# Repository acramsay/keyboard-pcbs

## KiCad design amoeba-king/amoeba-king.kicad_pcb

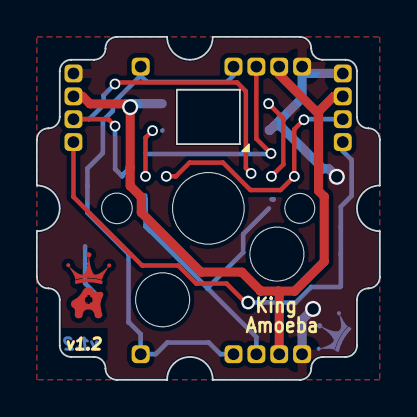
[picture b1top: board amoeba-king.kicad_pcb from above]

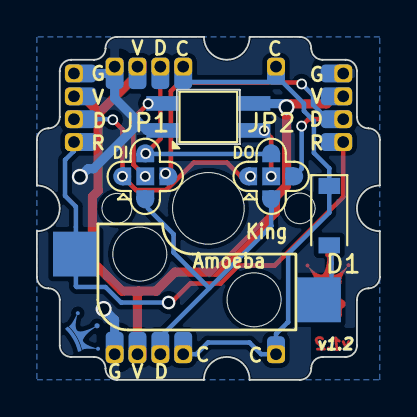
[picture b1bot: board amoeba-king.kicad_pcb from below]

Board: 2 copper layers, 19.0 x 19.1 mm, 14 parts (12 on the bottom side), 11 nets.

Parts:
Amoeba-Logo-Small: G***; amoeba-logo-small
D1: 1N4148W-7-F; D_SOD-123
J1, J4: Conn_01x04_Male; Header_1x04_P1.27mmL
J2, J3: Conn_01x04_Male; Header_1x04_P1.27mm
J5, J6: Conn_01x01_Male; Header_1x01_P1.27mm
JP1, JP2: SolderJumper_5; SolderJumper-5_P1.3mm_Open_RoundedPad1.0x1.5mm
LED1: SK6812MINI_E; LED_SK6812MINI_E_PLCC4_3.2x2.8mm_Shine_Through
Royale: G***; royale
Royale#2: G***; royale
S1: MX1A; Kailh_MX_Socket

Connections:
/C: D1.1 (K), J2.1, J4.1, J5.1, J6.1
/DIN: JP1.2 (C), LED1.4 (DIN)
/DOUT: JP2.2 (C), LED1.2 (DOUT)
/GND: J1.4, J2.4, J3.4, J4.4, LED1.3 (VSS)
/R: J1.1, J3.1, S1.1
/VDD: J1.3, J2.3, J3.3, J4.3, LED1.1 (VDD)
unnamed: D1.2 (A), S1.2
unnamed: J1.2, JP1.1 (A), JP2.1 (A)
unnamed: J2.2, JP1.5 (E), JP2.5 (E)
unnamed: J3.2, JP1.3 (B), JP2.3 (B)
unnamed: J4.2, JP1.4 (D), JP2.4 (D)
